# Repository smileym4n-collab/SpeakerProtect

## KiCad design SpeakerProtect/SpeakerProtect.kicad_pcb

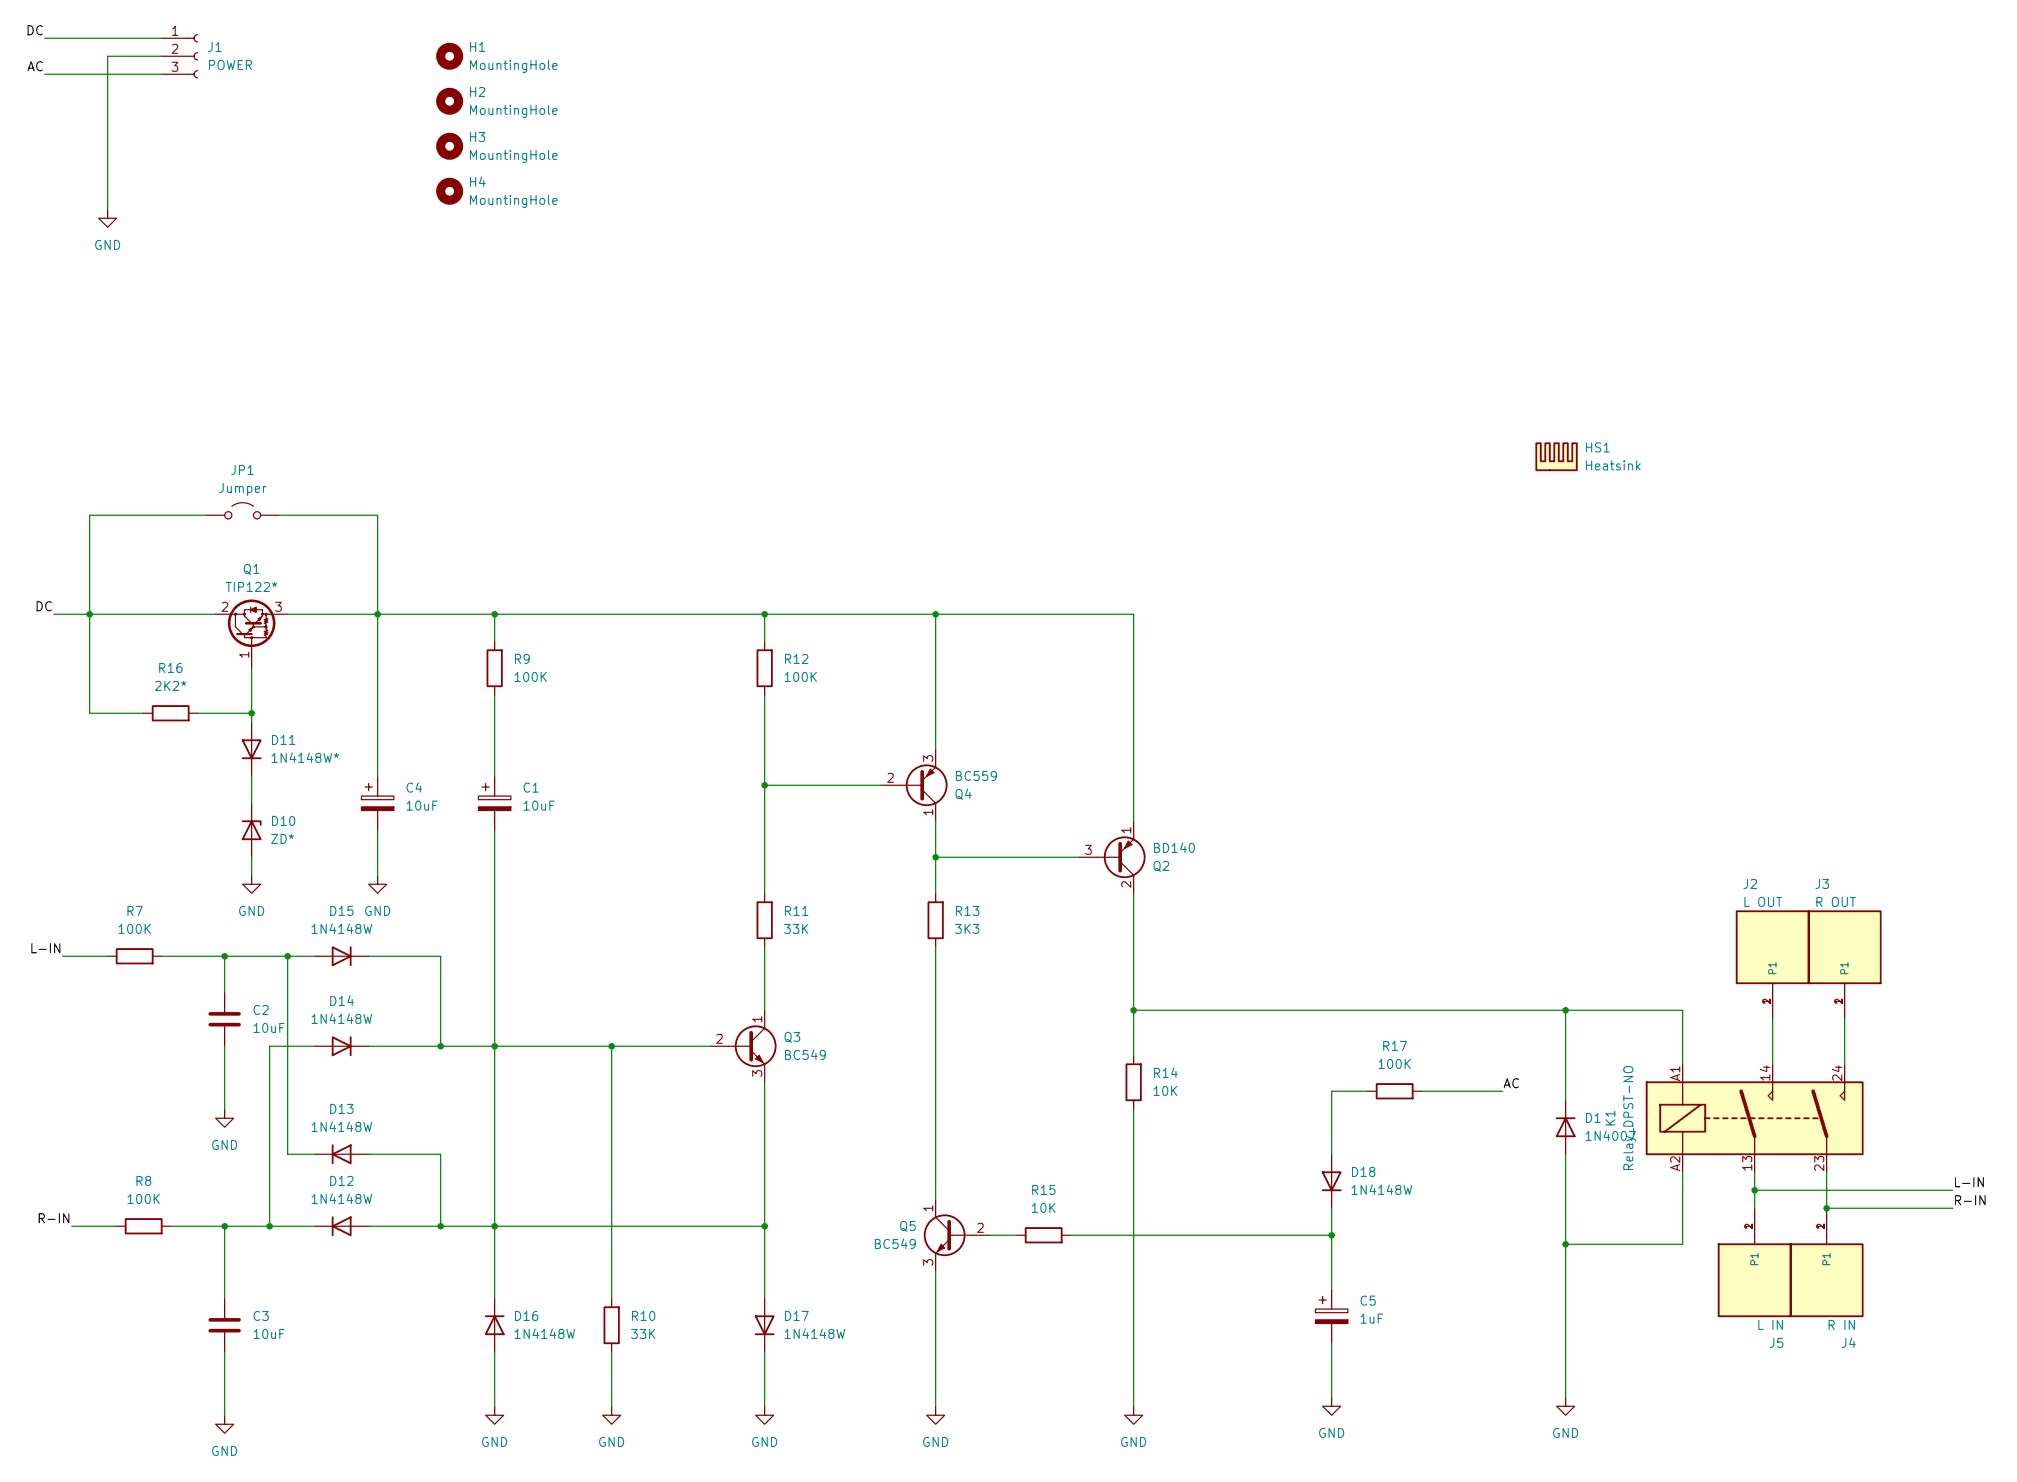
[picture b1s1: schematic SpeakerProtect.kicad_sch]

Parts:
C1, C4: 10uF; CP_Radial_D5.0mm_P2.00mm
C2, C3: 10uF; C_Radial_D6.3mm_H7.0mm_P2.50mm
C5: 1uF; CP_Radial_D5.0mm_P2.00mm
D1: 1N4007; D_DO-41_SOD81_P10.16mm_Horizontal
D10: ZD*; D_DO-41_SOD81_P10.16mm_Horizontal
D11: 1N4148W*; D_SOD-123
D12, D13, D14, D15, D16, D17, D18: 1N4148W; D_SOD-123
H1, H2, H3, H4: MountingHole; MountingHole_4mm
HS1: Heatsink; Tiny heatsink
J1: POWER; JST_XH_B3B-XH-A_1x03_P2.50mm_Vertical
J2: L OUT; TE_62409-1; PART_DESCRIPTION CONN QC TAB 0.250 SOLDER
J3: R OUT; TE_62409-1; PART_DESCRIPTION CONN QC TAB 0.250 SOLDER
J4: R IN; TE_62409-1; PART_DESCRIPTION CONN QC TAB 0.250 SOLDER
J5: L IN; TE_62409-1; PART_DESCRIPTION CONN QC TAB 0.250 SOLDER
JP1: Jumper; TestPoint_2Pads_Pitch5.08mm_Drill1.3mm
K1: Relay_DPST-NO; Relay_DPST_Omron_G2RL-2A
Q1: TIP122*; TO-220-3_Vertical
Q2: BD140; TO-126-3_Vertical
Q3, Q5: BC549; TO-92L_Inline_Wide
Q4: BC559; TO-92L_Inline_Wide
R7, R8, R9, R12, R17: 100K; R_0805_2012Metric_Pad1.20x1.40mm_HandSolder
R10, R11: 33K; R_0805_2012Metric_Pad1.20x1.40mm_HandSolder
R13: 3K3; R_0805_2012Metric_Pad1.20x1.40mm_HandSolder
R14, R15: 10K; R_0805_2012Metric_Pad1.20x1.40mm_HandSolder
R16: 2K2*; R_Axial_DIN0207_L6.3mm_D2.5mm_P10.16mm_Horizontal

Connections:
/AC: J1.3, R17.2
/DC: J1.1, JP1.1 (A), Q1.2 (C), R16.1
/L-IN: J5.1, J5.2 (P1), K1.13, R7.1
/R-IN: J4.1, J4.2 (P1), K1.23, R8.1
GND: C2.1, C3.1, C4.2, C5.2, D1.2 (A), D10.2 (A), D16.2 (A), D17.1 (K), J1.2, K1.A2, Q5.3 (E), R10.1, R14.1
unnamed: C1.1, R9.1
unnamed: D1.1 (K), K1.A1, Q2.2 (C), R14.2
unnamed: D10.1 (K), D11.1 (K)
unnamed: D11.2 (A), Q1.1 (B), R16.2
unnamed: C1.2, D12.2 (A), D13.2 (A), D14.1 (K), D15.1 (K), D16.1 (K), D17.2 (A), Q3.2 (B), Q3.3 (E), R10.2
unnamed: C3.2, D12.1 (K), D14.2 (A), R8.2
unnamed: C2.2, D13.1 (K), D15.2 (A), R7.2
unnamed: D18.2 (A), R17.1
unnamed: C5.1, D18.1 (K), R15.2
unnamed: J2.1, J2.2 (P1), K1.14
unnamed: J3.1, J3.2 (P1), K1.24
unnamed: C4.1, JP1.2 (B), Q1.3 (E), Q2.1 (E), Q4.3 (E), R9.2, R12.2
unnamed: Q2.3 (B), Q4.1 (C), R13.2
unnamed: Q3.1 (C), R11.1
unnamed: Q4.2 (B), R11.2, R12.1
unnamed: Q5.2 (B), R15.1
unnamed: Q5.1 (C), R13.1

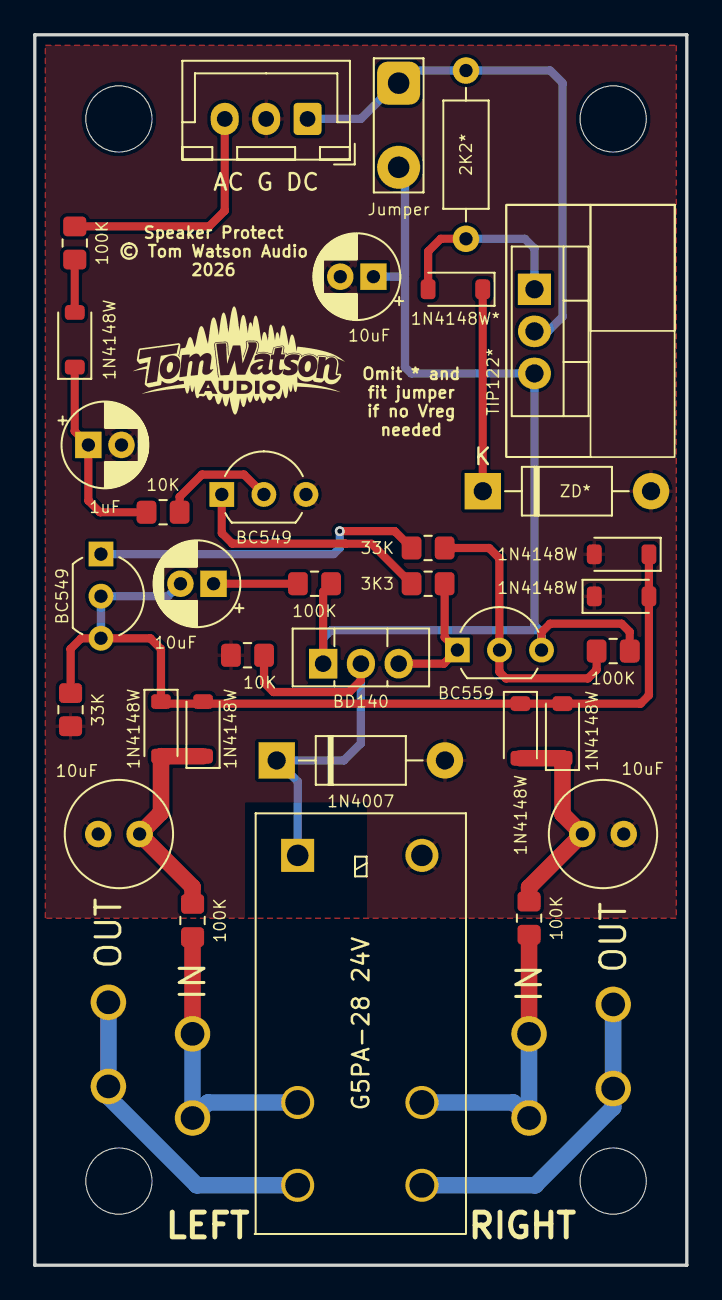
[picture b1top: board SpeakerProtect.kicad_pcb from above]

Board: 2 copper layers, 39.4 x 74.3 mm, 43 parts (0 on the bottom side), 22 nets.

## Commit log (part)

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2026-06-19 initial

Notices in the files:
SpeakerProtect/SpeakerProtect.kicad_pcb:
© Tom Watson Audio
